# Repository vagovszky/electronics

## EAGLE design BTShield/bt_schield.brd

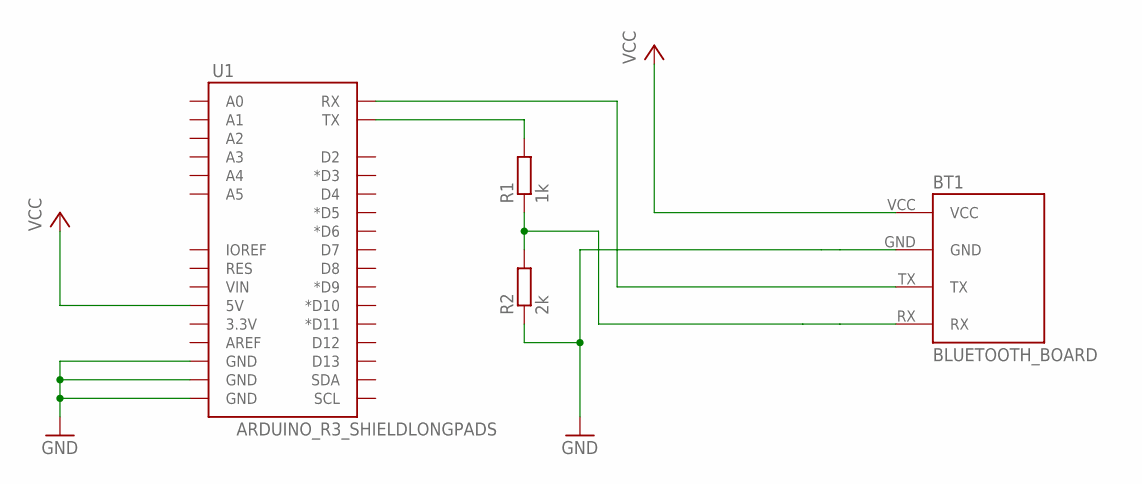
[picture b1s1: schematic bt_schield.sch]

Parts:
BT1: BLUETOOTH_BOARD; BT_BOARD_FOOTPRINT
R1: 1k; 0207/12
R2: 2k; 0207/12
U1: ARDUINO_R3_SHIELDLONGPADS; UNO_R3_SHIELD_LONGPADS

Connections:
GND: BT1.GND, R2.1, U1.GND@0 (GND), U1.GND@1 (GND), U1.GND@2 (GND)
unnamed: BT1.RX, R1.1, R2.2
unnamed: BT1.TX, U1.RX
unnamed: R1.2, U1.TX
VCC: BT1.VCC, U1.5V

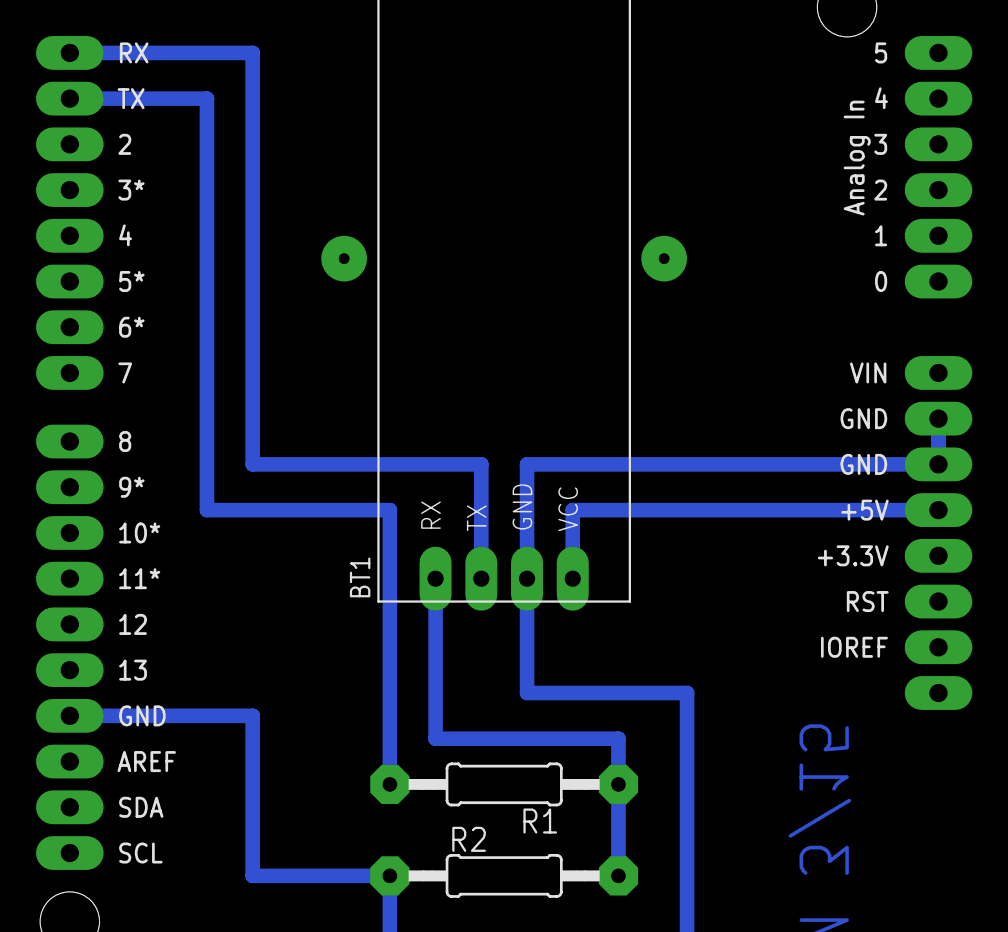
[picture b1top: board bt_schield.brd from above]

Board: 2 copper layers, 4 parts (0 on the bottom side), 5 nets.

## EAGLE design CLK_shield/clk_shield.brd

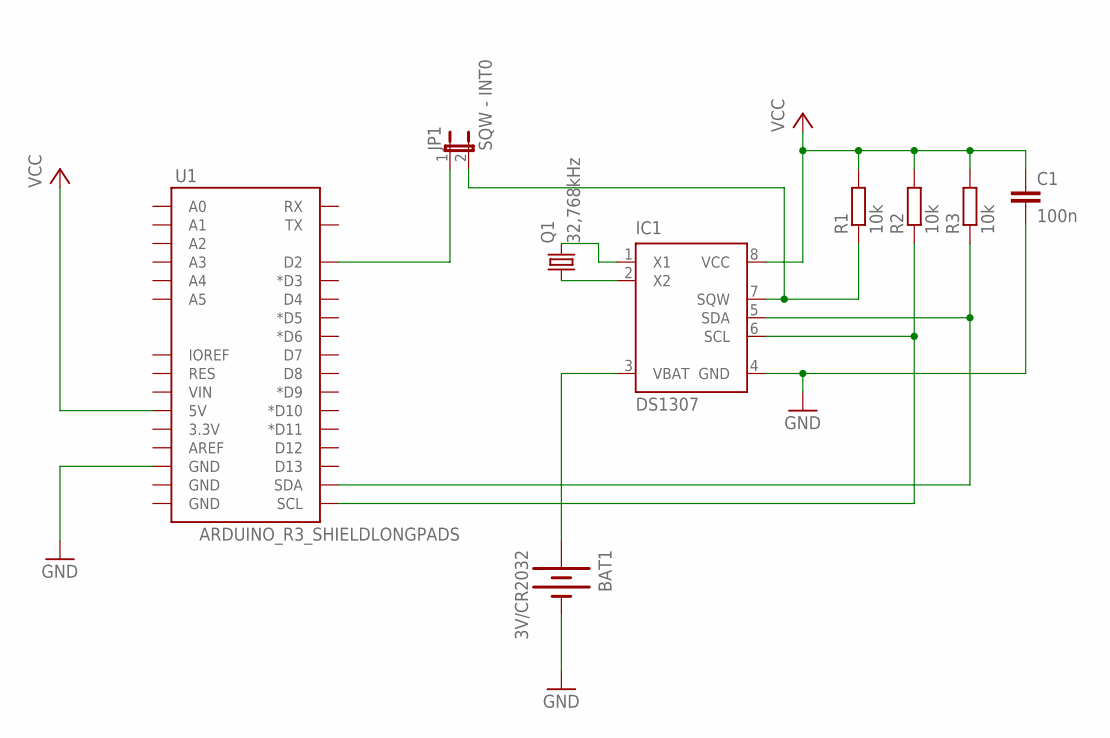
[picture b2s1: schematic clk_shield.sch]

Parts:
BAT1: 3V/CR2032; BATTCOM_20MM_PTH
C1: 100n; C050-025X075
IC1: DS1307; DIP-8
JP1: SQW - INT0; 1X02
Q1: 32,768kHz; TC26H
R1, R2, R3: 10k; 0207/12
U1: ARDUINO_R3_SHIELDLONGPADS; UNO_R3_SHIELD_LONGPADS

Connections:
GND: BAT1.2 (-), C1.2, IC1.4 (GND), U1.GND@2 (GND)
unnamed: BAT1.1 (+), IC1.3 (VBAT)
unnamed: IC1.1 (X1), Q1.2
unnamed: IC1.2 (X2), Q1.1
unnamed: IC1.6 (SCL), R2.1, U1.SCL
unnamed: IC1.5 (SDA), R3.1, U1.SDA
unnamed: JP1.1, U1.D2
unnamed: IC1.7 (SQW), JP1.2, R1.1
VCC: C1.1, IC1.8 (VCC), R1.2, R2.2, R3.2, U1.5V

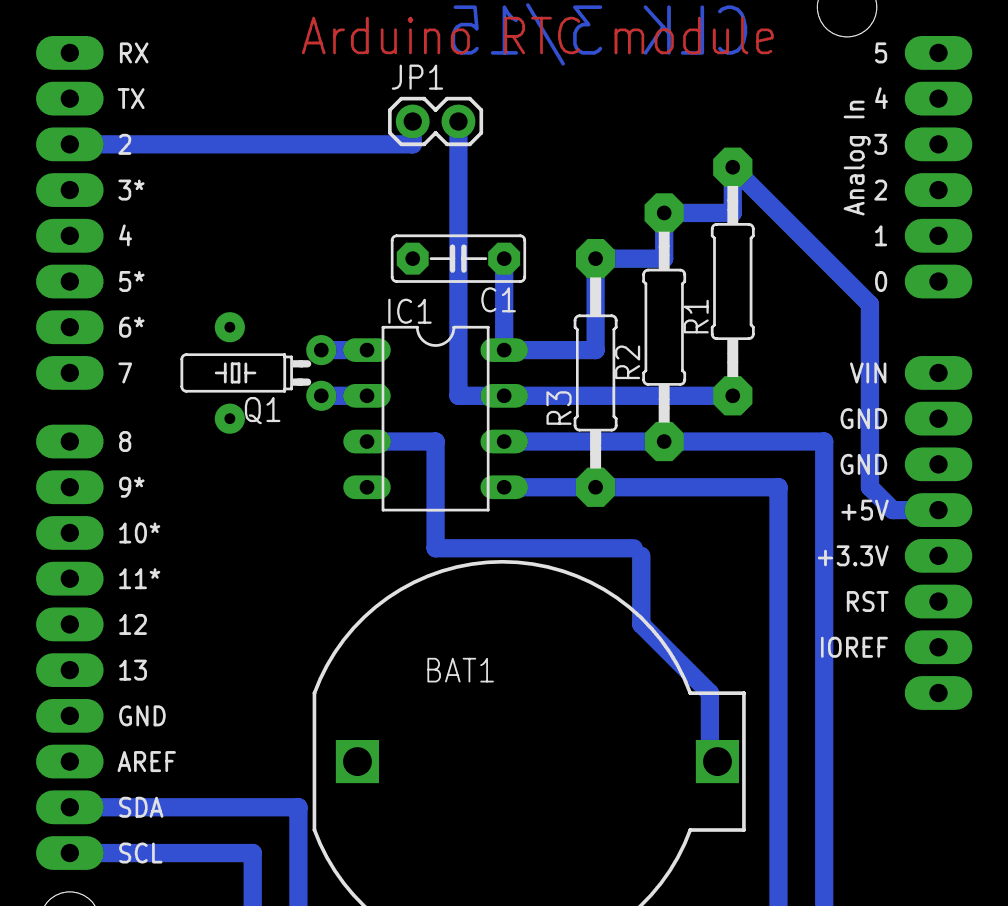
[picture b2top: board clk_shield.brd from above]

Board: 2 copper layers, 9 parts (0 on the bottom side), 9 nets.

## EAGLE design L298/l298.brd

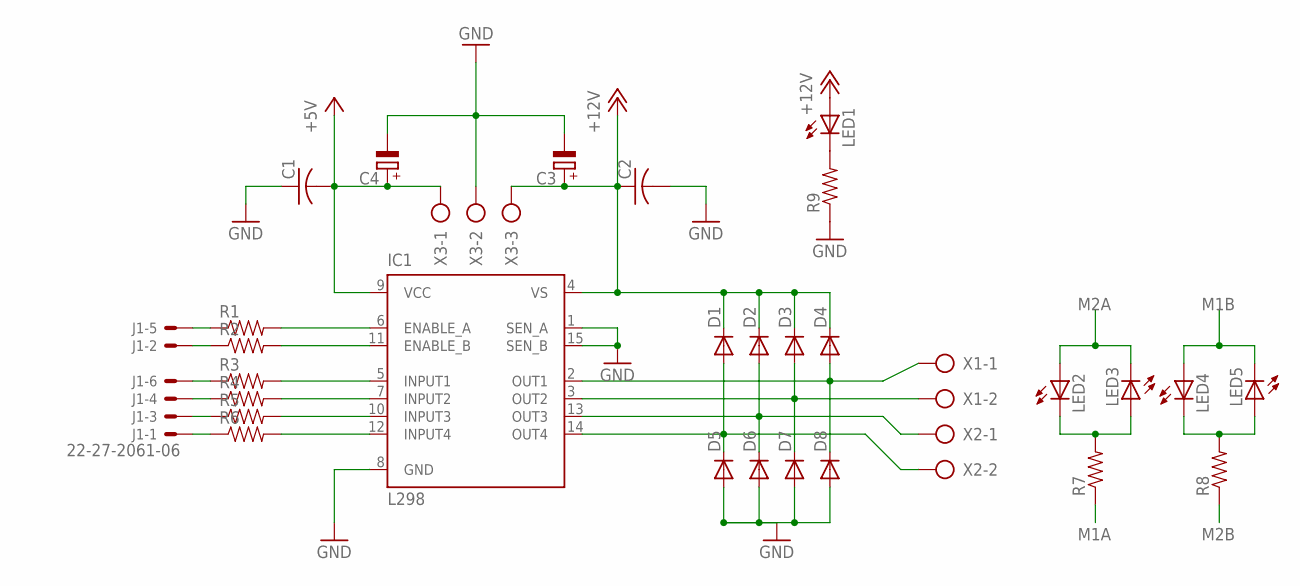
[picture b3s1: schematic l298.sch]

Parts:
C1, C2: C-US025-024X044; C025-024X044
C3: CPOL-EUE5-10.5; E5-10,5
C4: CPOL-EUE2-5; E2-5
D1, D2, D3, D4, D5, D6, D7, D8: DIODE1N4148; DIODE-1N4148
IC1: L298; MULTIWATT-15
J1: 22-27-2061-06; 6410-06
LED1, LED2, LED3, LED4, LED5: LED3MM
R1, R2, R3, R4, R5, R6, R7, R8, R9: RESISTORPTH-1/6W; 1/6W-RES
X1, X2: AK500/2
X3: AK500/3

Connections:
2A: IC1.10 (INPUT3), R5.2
+5V: C1.2, C4.+, IC1.9 (VCC), X3.1
+12V: C2.1, C3.+, D1.C, D2.C, D3.C, D4.C, IC1.4 (VS), LED1.A, X3.3
A1: IC1.5 (INPUT1), R3.2
B1: IC1.7 (INPUT2), R4.2
B2: IC1.12 (INPUT4), R6.2
GND: C1.1, C2.2, C3.-, C4.-, D5.A, D6.A, D7.A, D8.A, IC1.1 (SEN_A), IC1.8 (GND), IC1.15 (SEN_B), R9.1, X3.2
M1A: D4.A, D8.C, IC1.2 (OUT1), R7.1, X1.1
M1B: D2.A, D6.C, IC1.13 (OUT3), LED4.A, LED5.K (C), X2.1
M2A: D3.A, D7.C, IC1.3 (OUT2), LED2.A, LED3.K (C), X1.2
M2B: D1.A, D5.C, IC1.14 (OUT4), R8.1, X2.2
unnamed: J1.5, R1.1
unnamed: J1.2, R2.1
unnamed: J1.6, R3.1
unnamed: J1.4, R4.1
unnamed: LED4.K (C), LED5.A, R8.2
unnamed: LED2.K (C), LED3.A, R7.2
unnamed: J1.3, R5.1
unnamed: LED1.K (C), R9.2
unnamed: J1.1, R6.1
PWMA: IC1.6 (ENABLE_A), R1.2
PWMB: IC1.11 (ENABLE_B), R2.2

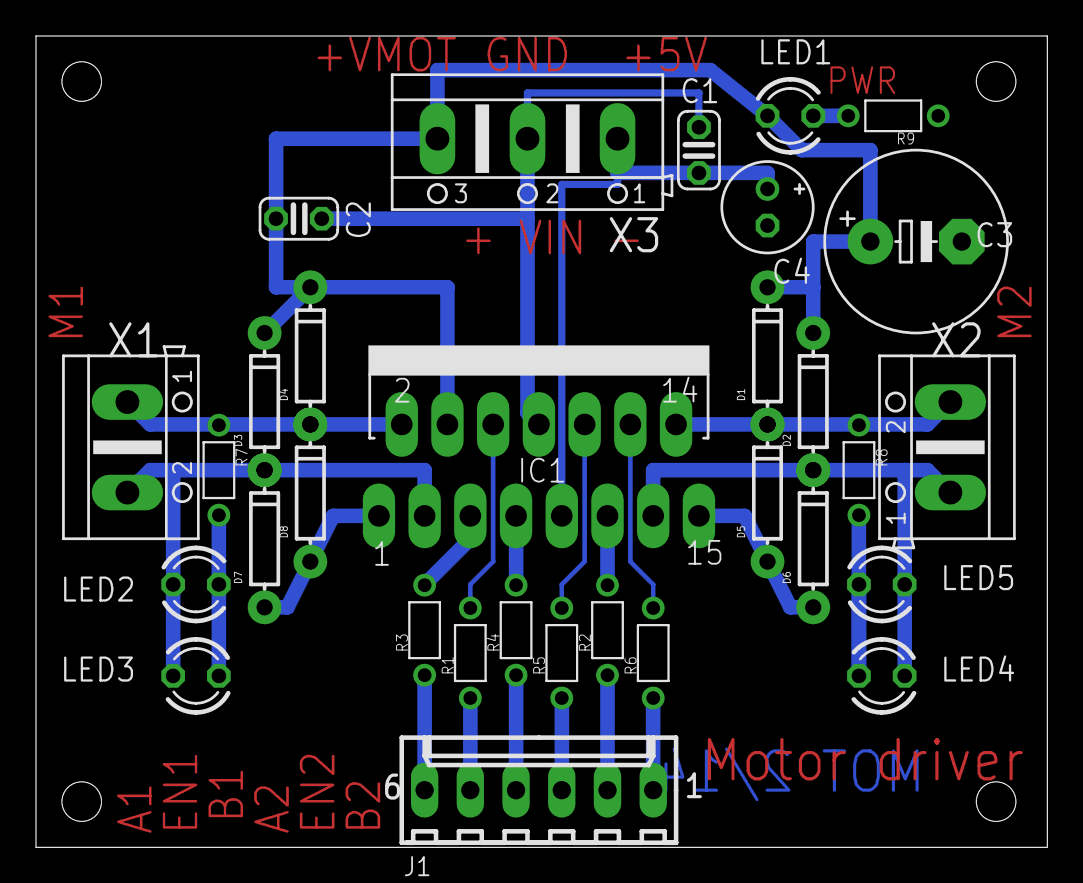
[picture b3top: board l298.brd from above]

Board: 2 copper layers, 56.2 x 45.1 mm, 31 parts (0 on the bottom side), 22 nets.

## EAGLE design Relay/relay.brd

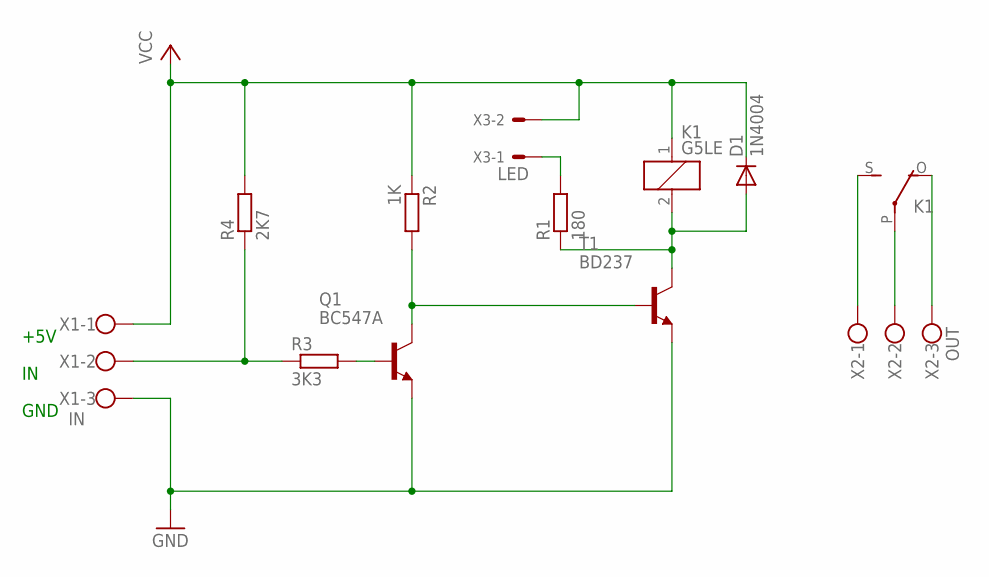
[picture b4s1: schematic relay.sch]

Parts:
D1: 1N4004; DO41-10
K1: G5LE
Q1: BC547A; TO92
R1: 180; 0207/10
R2: 1K; 0207/7
R3: 3K3; 0207/10
R4: 2K7; 0207/10
T1: BD237; TO126V
X1: IN; AK550/3
X2: OUT; W237-103
X3: LED; 6410-02

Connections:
GND: Q1.1 (E), T1.1 (E), X1.3
unnamed: K1.S, X2.1
unnamed: K1.P, X2.2
unnamed: K1.O, X2.3
unnamed: R3.1, R4.1, X1.2
unnamed: Q1.3 (C), R2.2, T1.3 (B)
unnamed: R1.2, X3.1
unnamed: Q1.2 (B), R3.2
unnamed: D1.A, K1.2, R1.1, T1.2 (C)
VCC: D1.C, K1.1, R2.1, R4.2, X1.1, X3.2

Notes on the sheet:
+5V
GND

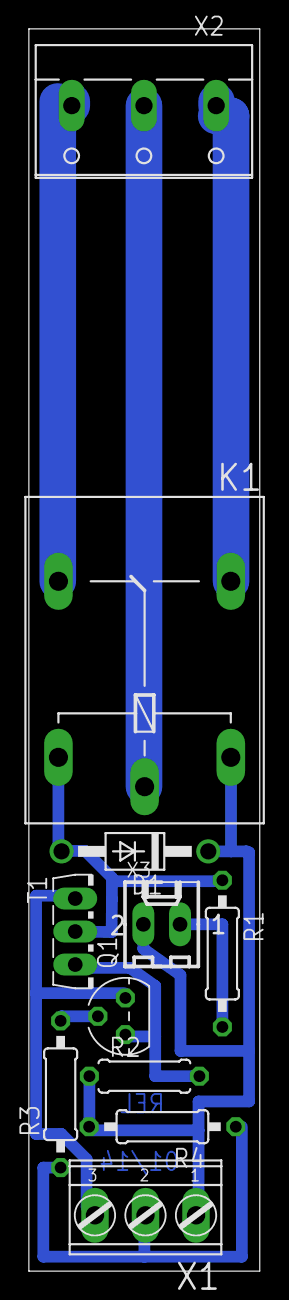
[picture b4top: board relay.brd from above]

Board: 2 copper layers, 16.0 x 86.0 mm, 11 parts (0 on the bottom side), 10 nets.

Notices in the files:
parts and their libraries:
My: Licensing: Creative Commons ShareAlike 4.0 International - https://creativecommons.org/licenses/by-sa/4.0
